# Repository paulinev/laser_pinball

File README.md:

laser_pinball
=============

6.111 final project 2014
IT'S OVER WOOOOOOOOOOOOOO

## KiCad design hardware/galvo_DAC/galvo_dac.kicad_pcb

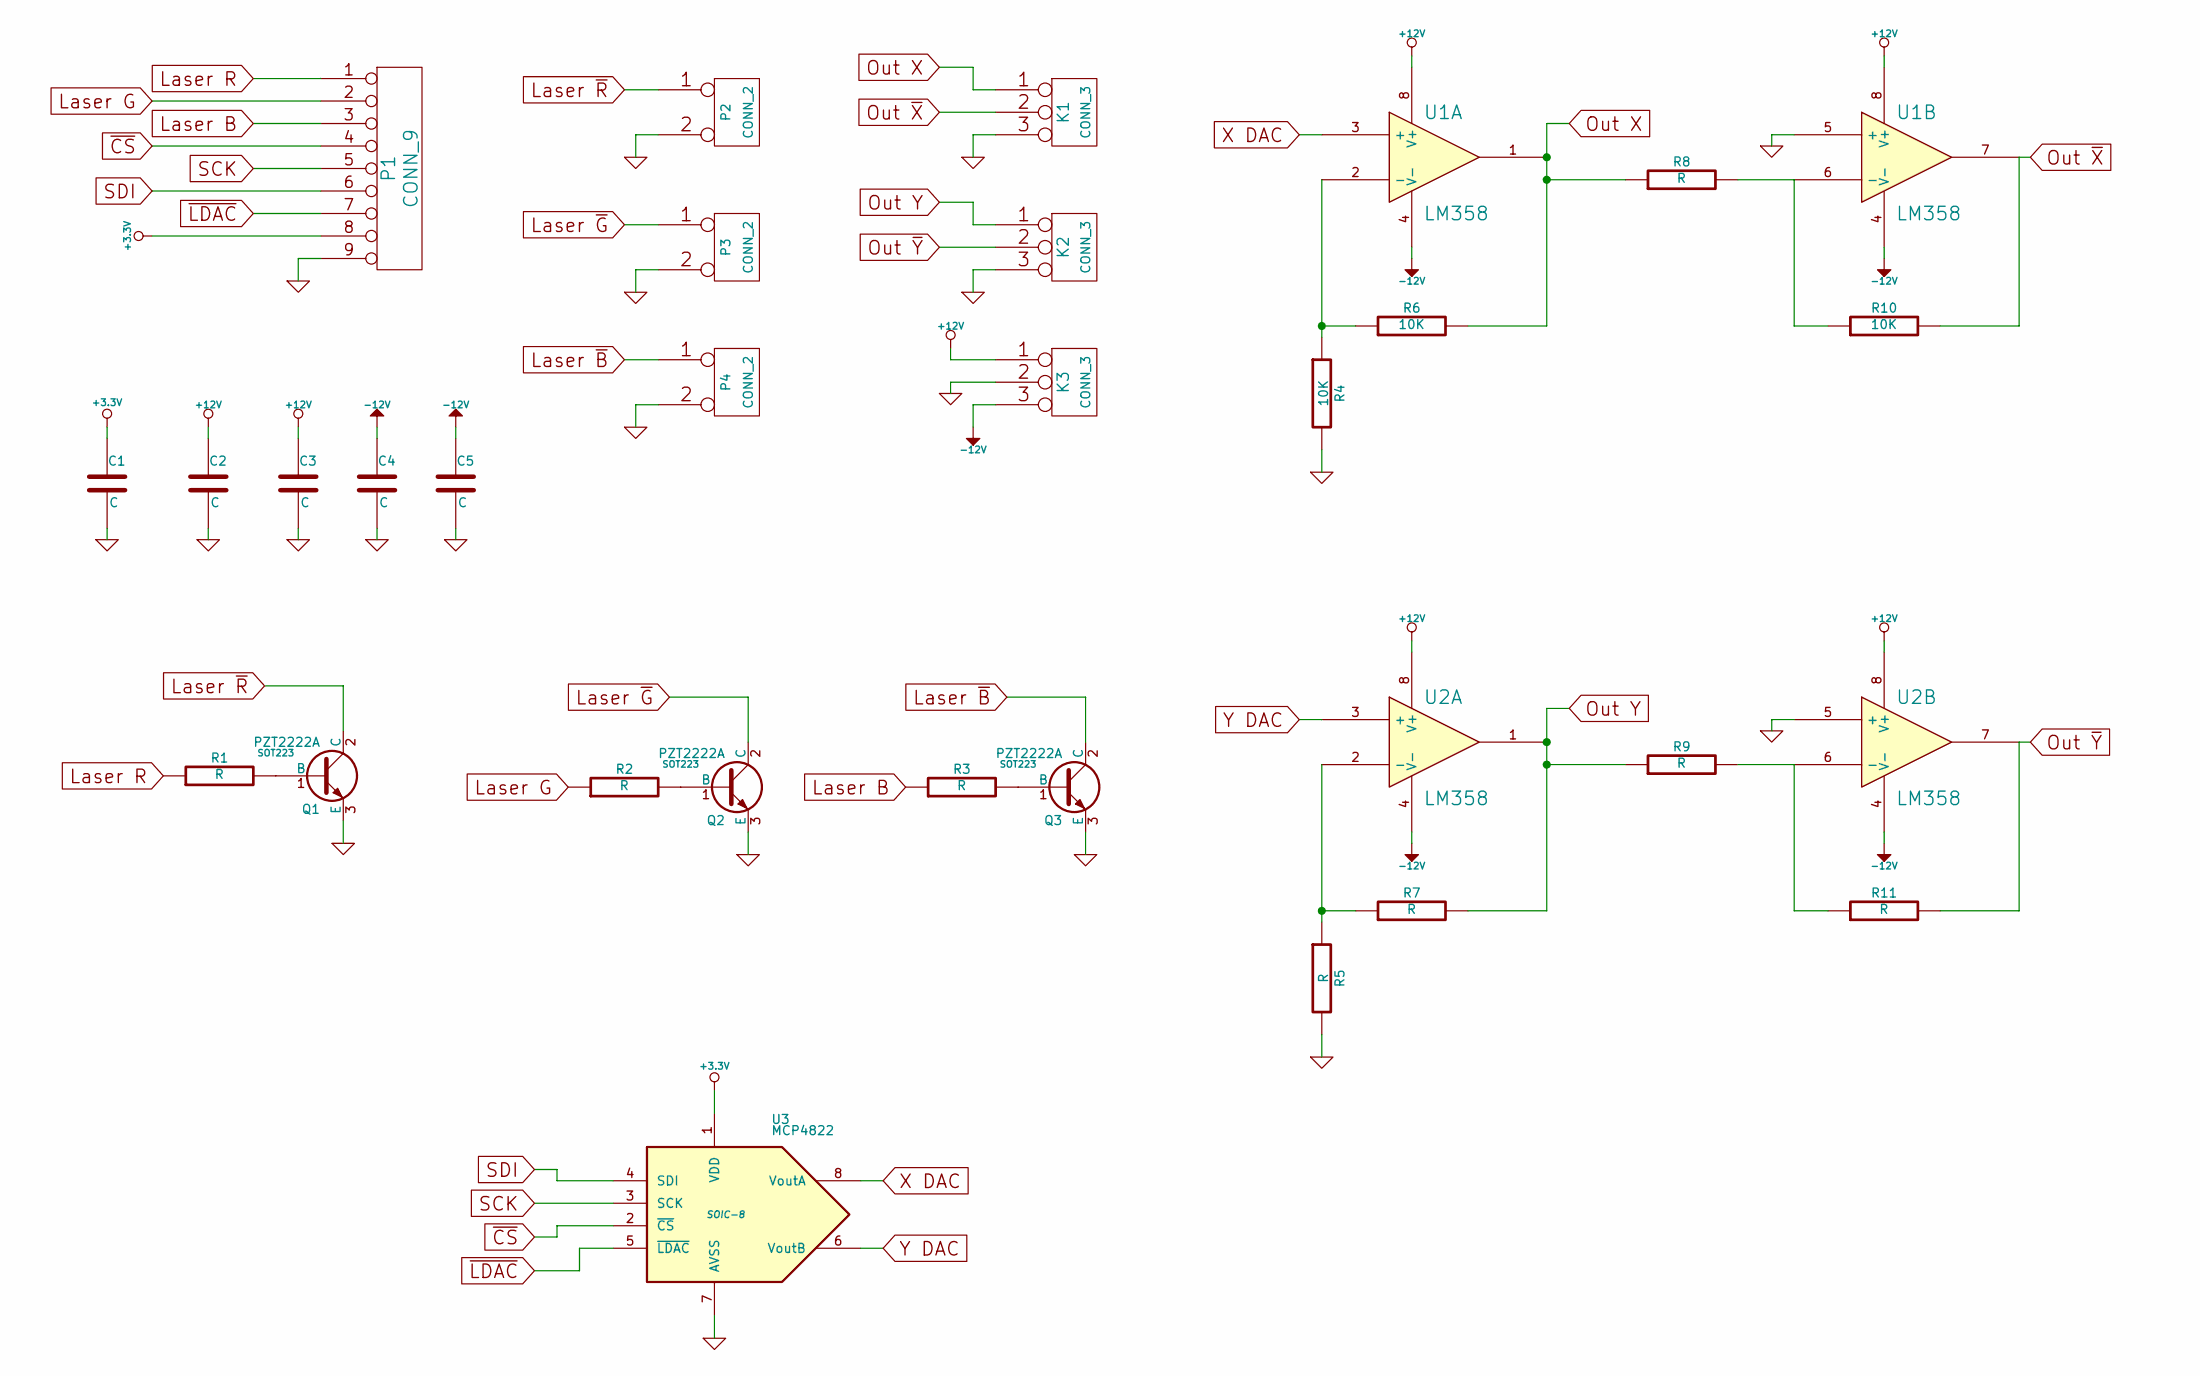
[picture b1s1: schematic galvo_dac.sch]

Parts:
C1, C2, C3, C4, C5: C
K1, K2, K3: CONN_3
P1: CONN_9
P2, P3, P4: CONN_2
Q1, Q2, Q3: PZT2222A; SOT223
R1, R2, R3, R5, R7, R8, R9, R11: R
R4, R6, R10: 10K
U1, U2: LM358
U3: MCP4822; SOIC-8

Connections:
+3.3V: C1.1, P1.8, U3.1 (VDD)
+12V: C2.1, C3.1, K3.1, U1.8 (V+), U2.8 (V+)
-12V: C4.1, C5.1, K3.3, U1.4 (V-), U2.4 (V-)
GND: C1.2, C2.2, C3.2, C4.2, C5.2, K1.3, K2.3, K3.2 (PM), P1.9, P2.2 (PM), P3.2 (PM), P4.2 (PM), Q1.3 (E), Q2.3 (E), Q3.3 (E), R4.2, R5.2, U1.5 (+), U2.5 (+), U3.7 (AVSS)
Laser B: P1.3, R3.1
Laser G: P1.2, R2.1
Laser R: P1.1, R1.1
Laser ~B~: P4.1, Q3.2 (C)
Laser ~G~: P3.1, Q2.2 (C)
Laser ~R~: P2.1, Q1.2 (C)
unnamed: Q1.1 (B), R1.2
unnamed: Q2.1 (B), R2.2
unnamed: Q3.1 (B), R3.2
unnamed: R4.1, R6.1, U1.2 (-)
unnamed: R5.1, R7.1, U2.2 (-)
unnamed: R8.2, R10.1, U1.6 (-)
unnamed: R9.2, R11.1, U2.6 (-)
Out X: K1.1, R6.2, R8.1, U1.1
Out Y: K2.1, R7.2, R9.1, U2.1
Out ~X~: K1.2 (PM), R10.2, U1.7
Out ~Y~: K2.2 (PM), R11.2, U2.7
SCK: P1.5, U3.3 (SCK)
SDI: P1.6, U3.4 (SDI)
X DAC: U1.3 (+), U3.8 (VoutA)
Y DAC: U2.3 (+), U3.6 (VoutB)
~CS~: P1.4, U3.2 (~CS~)
~LDAC~: P1.7, U3.5 (~LDAC~)

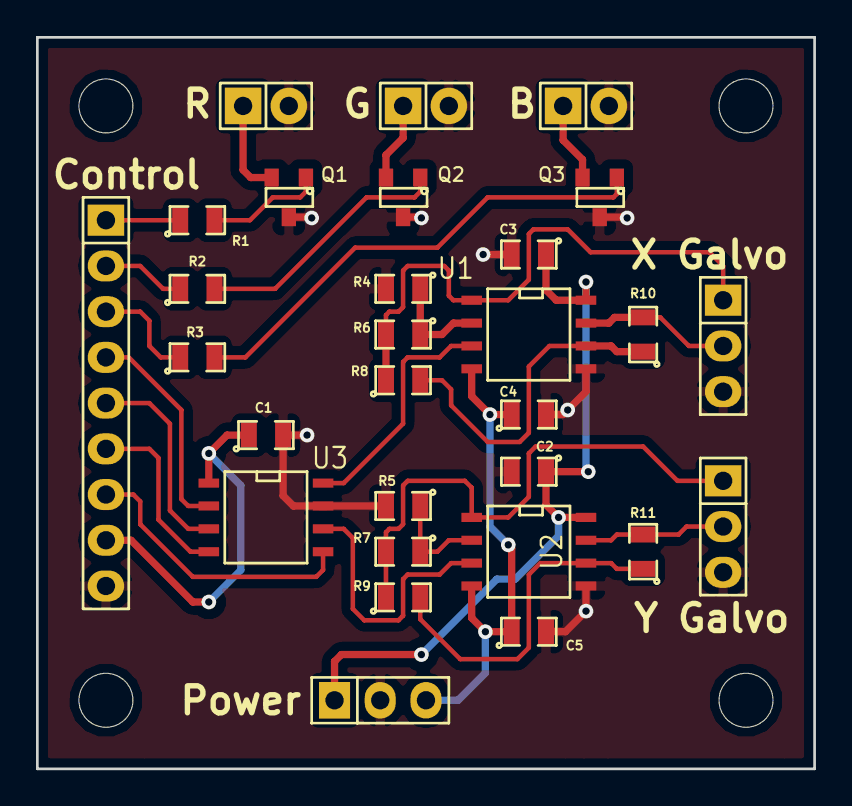
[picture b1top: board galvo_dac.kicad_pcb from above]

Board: 2 copper layers, 43.2 x 40.6 mm, 33 parts (0 on the bottom side), 27 nets.

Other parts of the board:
MH: MountingHole_3mm_RevA_Date21Jun2010; MountingHole_3mm
MH#2, MH#3, MH#4: MountingHole_3mm_RevA_Date21Jun2010; MountingHole_3mm

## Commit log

2014-11-16 Create sccb_master.v
    Version 0, untested, SCCB bus.
2014-11-16 Restructured directory.
2014-11-16 Create i2c_master.v
    Read-only, untested.
2014-11-16 updated README.txt
2014-11-16 Create clock_divider.v
    Clock divider for I2C and SCCB, assumes 1MHz starting clock to divide down to 100kHz (change with parameter "delay").
2014-11-16 Added README.txt
2014-11-18 Added files from preliminary testing in ISE.
2014-11-18 Two-phase write/read test; worked out kinks in three-phase write. SCCB probably working.
2014-11-18 Working on camera read
2014-11-19 Camera reader and BRAM frame buffer.
2014-11-19 added Nexys 3 ucf and beta.v
2014-11-20 added beta test files
2014-11-20 Pre-testing save
2014-11-20 Failed attempt to display camera output on VGA.
2014-11-21 Created project for test compiling the beta on the nexys3
2014-11-21 Added galvo driver files
2014-11-21 Added testbenches
2014-11-22 Added Nexys3 test project
2014-11-24 added bsim files; beta now runs on nexys 3 board
2014-11-24 Include logic analyzer outputs.
2014-11-24 beta testing on nexys3
2014-11-24 added beta reference files
2014-11-24 restructured directory to be less stupid
2014-11-24 bleep
2014-11-24 blargh
2014-11-24 add nexys2 files
2014-11-24 Solved DCM syntax error
2014-11-24 Fixed CCLK to JTAG CLK on startup
2014-11-24 Remove extra file
2014-11-24 Update Nexys2 bit file
2014-11-24 More bitfile testing for Nexys2
2014-11-25 Fixed issues with camera read, BRAM read/write is still broken.
2014-11-25 Created interface pcb
2014-11-25 Finished PCB, sent to Fab
2014-11-25 Now there is at least an image! (Not a recognizeable one, but still.)
2014-11-26 Outlined new architecture for vector graphics module. Two betas, whoo!
2014-11-26 Update Nexys2 files
2014-11-26 Have most of the two betas set up
2014-11-27 backing up so I can make changes to try to get the beta to simulate
2014-11-27 Betas simulate! need to finsh up memory mapped IO
2014-11-27 I got two betas up and running on hardware with custom mapped IO
2014-11-28 Added beta mult inst and added SPI. Still need to test both with beta assembly
2014-11-30 the beta stuff is finished?
2014-11-30 Added beta address space documentation
2014-11-30 Tested multiply, ran simple test program. There seems to be an issue with branches?
2014-11-30 Fixed beta opcode issue. Tested memory mapped IO interfaces
2014-12-03 Have a working I2C block
2014-12-03 VGA works! I have a green square!
2014-12-04 Assembly for laser driver
2014-12-04 Test program to draw square on laser galvos
    relative_load_test: Confirm operation of load and store instructions
2014-12-05 camera works. except no color?
2014-12-05 Include SPI configuration
2014-12-05 Camera works. Nothing like spending 8 hours tracking down a undocumented register someone on the internet told you about...
2014-12-05 Generate .coe
2014-12-05 created final project build
2014-12-05 Updated documentation, tested SPI write
2014-12-05 Adding minor changes to main laser driver code
2014-12-06 Adding updated .coe for laser test
2014-12-06 Fixed bug with timer initialization in COE
2014-12-06 actually actually fixed (spi data width)
2014-12-06 updated documentation, enabled interupt
2014-12-06 add NOP at beginning of draw test
2014-12-06 added clk constraint to UCF file
2014-12-06 got physics update loops and external memory writes working
2014-12-06 fixed reset issue
2014-12-06 adding driver coe
2014-12-06 coe update
2014-12-06 Update coe for test with physics beta
2014-12-06 updated external memory write
2014-12-06 fucked up a lil but its kay nao
2014-12-06 bleeeeeeeble
2014-12-06 floop
2014-12-06 add physics test results; both betas can interact
2014-12-07 restructured, updatated coes to fix reset issue
2014-12-07 blorp
2014-12-07 five bee one thirty-threeb
2014-12-07 Started on image recognition
2014-12-07 update driver asm
2014-12-07 smunt: anus paper! use it to make your anus less filthy
2014-12-07 this better not fuck up
2014-12-07 an eagle vagina
2014-12-07 update driver files
2014-12-07 flarples
2014-12-07 Worked on image processing FSM
2014-12-07 smorf
2014-12-07 derrr
2014-12-07 derrrrrrrrrr
2014-12-07 have a image displaying with new setup
2014-12-08 minty update
2014-12-08 minty update pt 3
2014-12-08 i'm hungry
2014-12-08 i'm hungryyyyy
2014-12-08 added corner stops or WHATEVS
2014-12-08 built some shit
2014-12-08 did the thing
2014-12-08 now i have a friggin config file
2014-12-08 lololol
2014-12-08 ARGH
2014-12-08 FUUUUUUUUU
2014-12-08 YOU ATE MY MINTS, BITCH
2014-12-08 today i was going to cry, sleep, and eat, but I only had time for one
2014-12-08 it's hard to motivate yourself to fix a compile-time syntax error when you can buy a powder that turns a house into a monster.
2014-12-08 more minty sprites
2014-12-08 add minty sprites in physics code
2014-12-08 working on controller interface
2014-12-08 i fixed a fuckup
2014-12-08 Removed files that shouldn't be tracked
2014-12-08 #helpfulgabe
2014-12-08 test one circle
2014-12-08 Image tracking sort of works!
2014-12-08 ahhhhhhhhhhhhhhhhhhhhhhhhhhhhhhhhhhhhhhhhhhhhh CANADAAAAAAAAAAAAAAAAAA
2014-12-08 lik dis if you cry evertim
2014-12-08 NES controller interface works
2014-12-08 pushing current changes to math tests
2014-12-08 restructured, fixed sprite library
2014-12-08 really hope this merge thing doesn't fuck anything up
2014-12-08 fixed table
2014-12-08 el oh el
2014-12-08 hopefully revert to last working state
2014-12-08 add flipper control
2014-12-08 your baby is crazygit pull
2014-12-10 Finished camera stuff
2014-12-10 Add report
2014-12-10 Edited the report a lot
2014-12-10 Added review and conclusion
2014-12-10 Added the rest of the physics stuff
2014-12-10 Sooooo it's 77 pages long
2014-12-10 Done?
